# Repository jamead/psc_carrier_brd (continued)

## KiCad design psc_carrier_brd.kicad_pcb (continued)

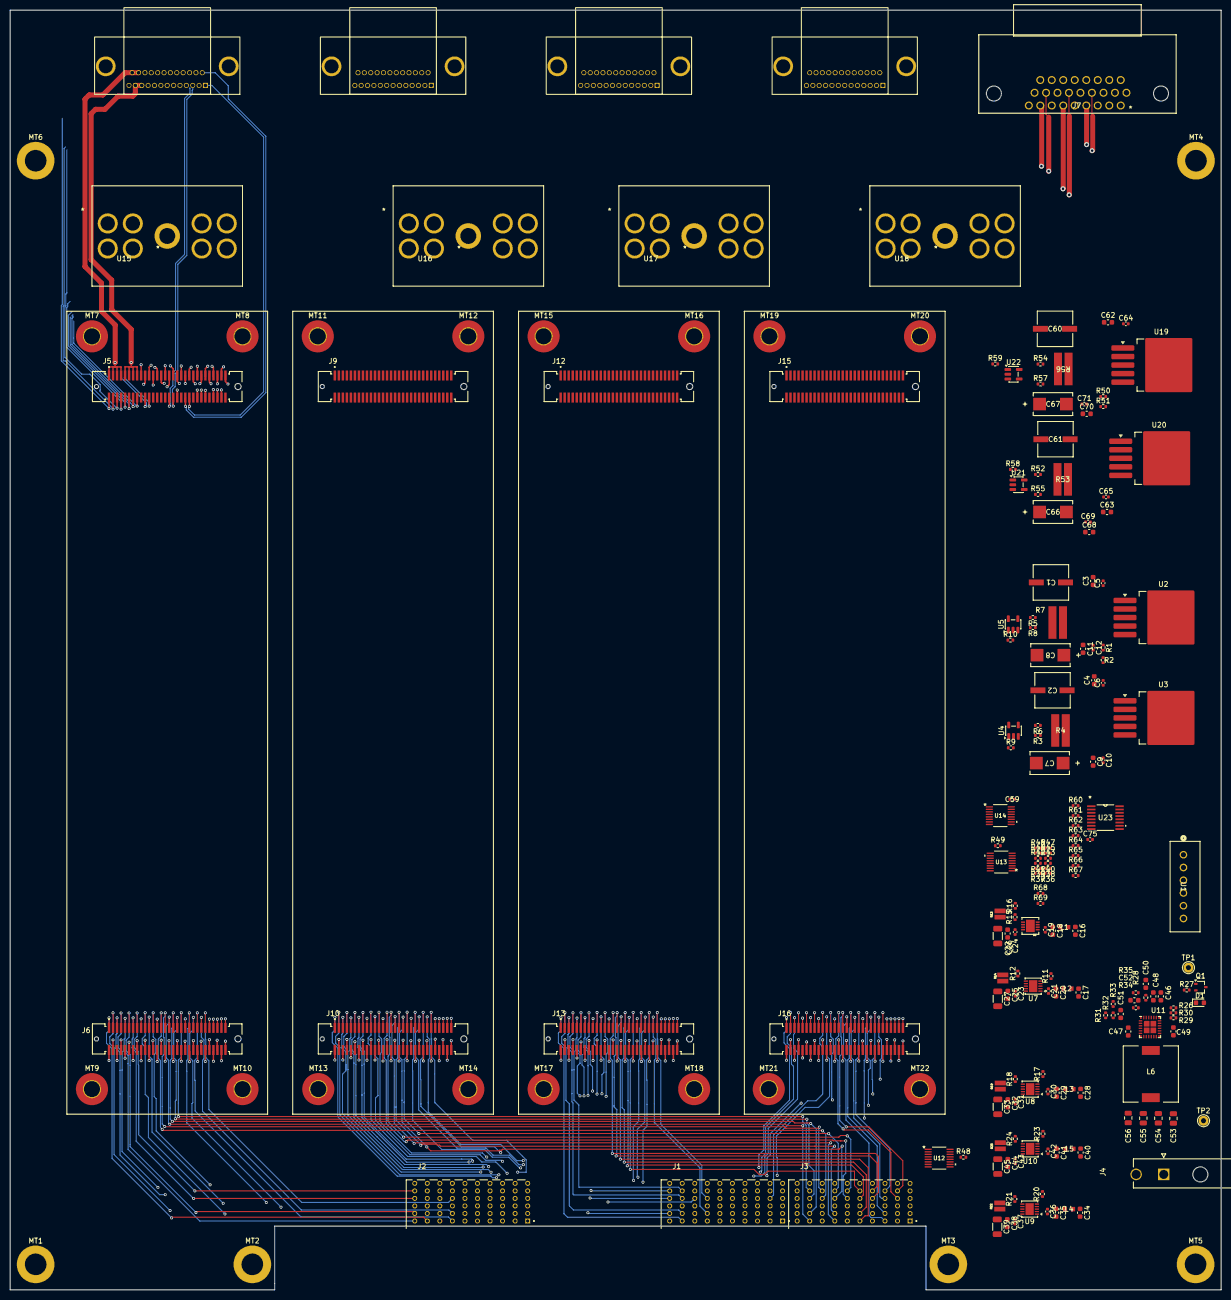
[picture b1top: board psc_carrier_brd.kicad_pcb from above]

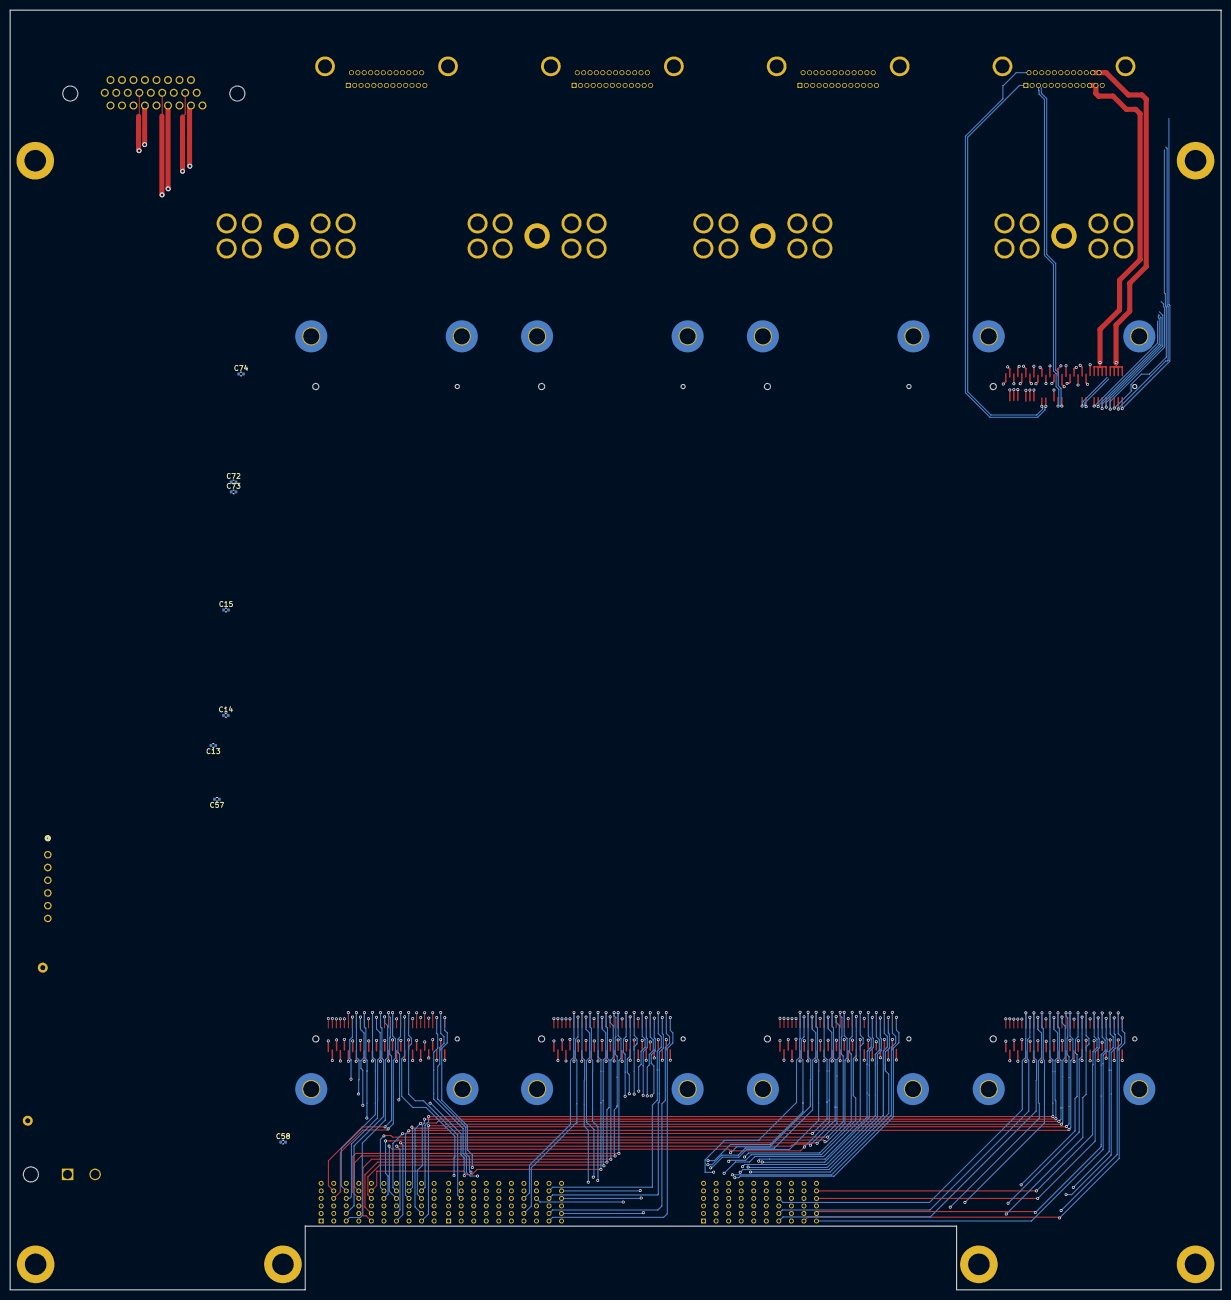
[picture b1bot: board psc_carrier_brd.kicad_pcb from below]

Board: 10 copper layers, 241.3 x 255.0 mm, 216 parts (8 on the bottom side), 277 nets.

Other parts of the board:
C46: 0.022u; C_0603_1608Metric
C47, C49: 10u; C_0603_1608Metric
C48, C52: 10p; C_0603_1608Metric
C50: 330p; C_0603_1608Metric
C51: 1u; C_0603_1608Metric
C53, C54, C55, C56: 22u; C_0805_2012Metric
D1: GREEN; LED_0603_1608Metric
Q1: NX7002BKW; SOT-323_SC-70
R26: 41.2k; R_0402_1005Metric
R27: 1k; R_0402_1005Metric
R28: 8.45k; R_0402_1005Metric
R29, R35: 10.2k; R_0402_1005Metric
R30: 1.13k; R_0402_1005Metric
R31, R32: 4.7k; R_0402_1005Metric
R33: 0; R_0402_1005Metric
R34: 42.2k; R_0402_1005Metric
TP1: Net-(Q1-G); TestPoint_THTPad_D2.0mm_Drill1.0mm
TP2: +5.0V; TestPoint_THTPad_D2.0mm_Drill1.0mm
U11: LT8643S; QFN-24-4EP_4x4mm_P0.5mm_EP1.125x1.125mm

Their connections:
unnamed: C50.1, R28.2
unnamed: D1.1 (K), R27.1
unnamed: Q1.3 (D), R27.2
unnamed: Q1.1 (G), R31.1, TP1.1, U11.23 (PG)
unnamed: R29.2, R30.1, U11.17 (EN/UV)
unnamed: C52.2, R34.2, R35.1, U11.24 (FB)
unnamed: C51.1, R31.2, R33.1, U11.2 (INTVCC)
unnamed: R26.1, U11.18 (RT)
unnamed: R32.1, R33.2, U11.20 (SYNC/MODE)
unnamed: C46.1, U11.21 (TR/SS)
unnamed: C48.1, R28.1, U11.22 (VC)

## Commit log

2025-06-22 Initial push
2025-06-24 Create 6469028-1 symbol
2025-06-24 Create custom NSLS2 worksheet
2025-06-26 Add symbol for PS connector
2025-06-26 Add footprint for PS connector
2025-06-27 Add board outline
2025-06-30 Upgrade to KiCad 9. Add all I/O connectors
2025-07-01 Add 3d model for DCCT connector
2025-07-02 Add DAC schematic page
2025-12-01 finish up regulator section
2025-12-03 Add all 4 channels
2025-12-15 Start routing
2025-12-15 Change board size length to 255mm
2025-12-30 Finished layout
2025-12-30 Tweak a few things
2026-01-05 tweak BOM
2026-01-06 Add Drawing Number
